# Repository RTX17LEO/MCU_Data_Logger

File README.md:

This is 4 layer verison of MCU Data Logger

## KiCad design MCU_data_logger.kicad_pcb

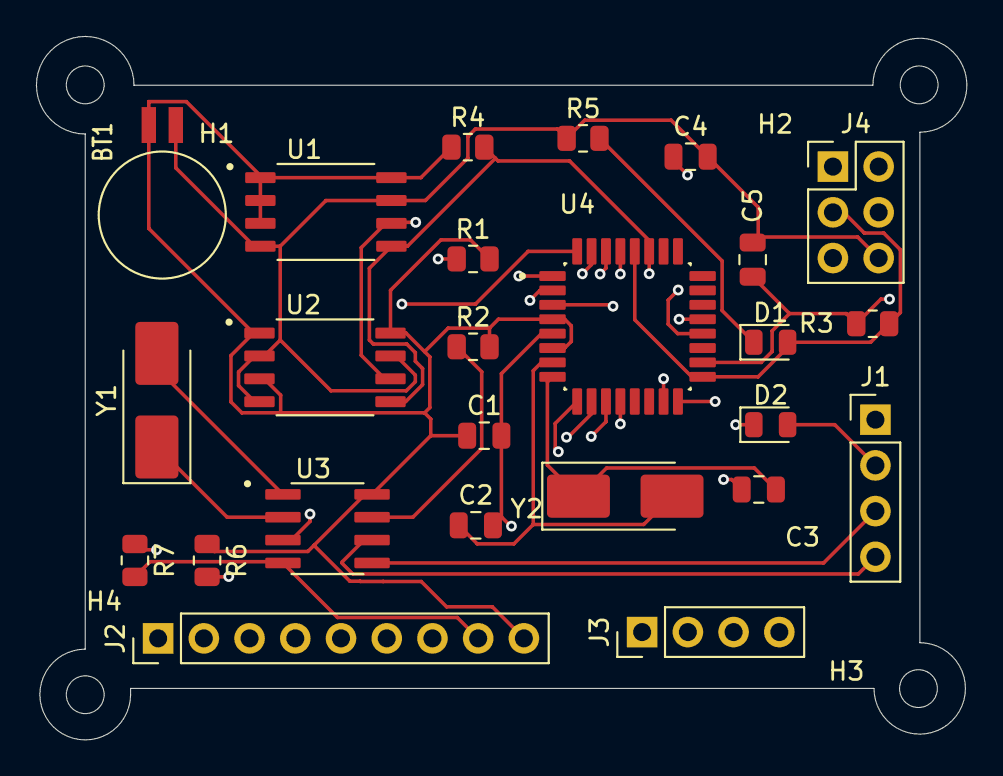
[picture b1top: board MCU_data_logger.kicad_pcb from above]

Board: 4 copper layers, 51.7 x 39.1 mm, 29 parts (0 on the bottom side), 25 nets.

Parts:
BT1: Battery; BatteryHolder_Seiko_MS621F
C1, C4: 0.1uF; C_0805_2012Metric
C2, C3: 22pF; C_0805_2012Metric
C5: 100nF; C_0805_2012Metric
D1, D2: LED; LED_0805_2012Metric
H1, H3: H1; MountingHole_2.1mm
H2, H4: MountingHole; MountingHole_2.1mm
J1: I2C; PinHeader_1x04_P2.54mm_Vertical
J2: GPIO; PinHeader_1x09_P2.54mm_Vertical
J3: SERIAL; PinHeader_1x04_P2.54mm_Vertical
J4: ICSP; PinHeader_2x03_P2.54mm_Vertical
R1, R2, R6: 10k; R_0805_2012Metric
R3, R4: 4.7k; R_0805_2012Metric
R5, R7: 330; R_0805_2012Metric
U1, U2: 24LC1025
U3: DS1337S_
U4: ATMEGA328P-AU; QFP80P900X900X120-32N
Y1: 32.768MHz; Crystal_SMD_5032-2Pin_5.0x3.2mm_HandSoldering
Y2: 16MHz; Crystal_SMD_5032-2Pin_5.0x3.2mm_HandSoldering

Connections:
/D2: J2.1, U4.32 (PD2)
/D3: J2.2, U4.1 (PD3)
/D4: J2.3, U4.2 (PD4)
/D5: J2.4, U4.9 (PD5)
/D6: J2.5, U4.10 (PD6)
/D7: J2.6, U4.11 (PD7)
/D8: J2.7, U4.12 (PB0)
/MISO: J4.1, U4.16 (PB4)
/MOSI: J4.4, U4.15 (PB3)
/RESET: J4.5, R6.2, U4.29 (PC6/~RESET)
/RX: J3.3, U4.30 (PD0)
/TX: J3.4, U4.31 (PD1)
/sck: D1.2 (A), J1.4, J4.3, R3.2, U1.6 (SCL), U2.6 (SCL), U3.6 (SCL), U4.17 (PB5), U4.28 (PC5)
/sda: J1.3, R4.2, U1.5 (SDA), U2.5 (SDA), U3.5 (SDA), U4.27 (PC4)
GND: BT1.2 (-), C1.2, C2.2, C3.1, C4.2, C5.2, J1.1, J2.8, J3.1, J4.6, R5.1, R7.2, U1.4 (GND), U1.7 (WP), U2.2 (A1), U2.4 (GND), U2.7 (WP), U3.4 (GND), U4.3 (GND), U4.5 (GND), U4.21 (GND)
unnamed: D1.1 (K), R5.2
unnamed: D2.1 (K), R7.1
unnamed: R2.1, U3.7 (SQW/~INT)
unnamed: U3.1 (X1), Y1.2
unnamed: U3.2 (X2), Y1.1
unnamed: R1.1, U3.3 (~INTA)
unnamed: C4.1, U4.20 (AREF)
unnamed: C2.1, U4.7 (PB6), Y2.2
unnamed: C3.2, U4.8 (PB7), Y2.1
VCC: BT1.1 (+), C1.1, C5.1, D2.2 (A), J1.2, J2.9, J3.2, J4.2, R1.2, R2.2, R3.1, R4.1, R6.1, U1.1 (A0), U1.2 (A1), U1.3 (A2), U1.8 (VCC), U2.1 (A0), U2.3 (A2), U2.8 (VCC), U3.8 (VCC), U4.4 (VCC), U4.6 (VCC), U4.18 (AVCC)

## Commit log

2026-06-26 2 layer PCB initial
2026-06-26 test change
2026-06-26 Converted to 4 layer PCB
